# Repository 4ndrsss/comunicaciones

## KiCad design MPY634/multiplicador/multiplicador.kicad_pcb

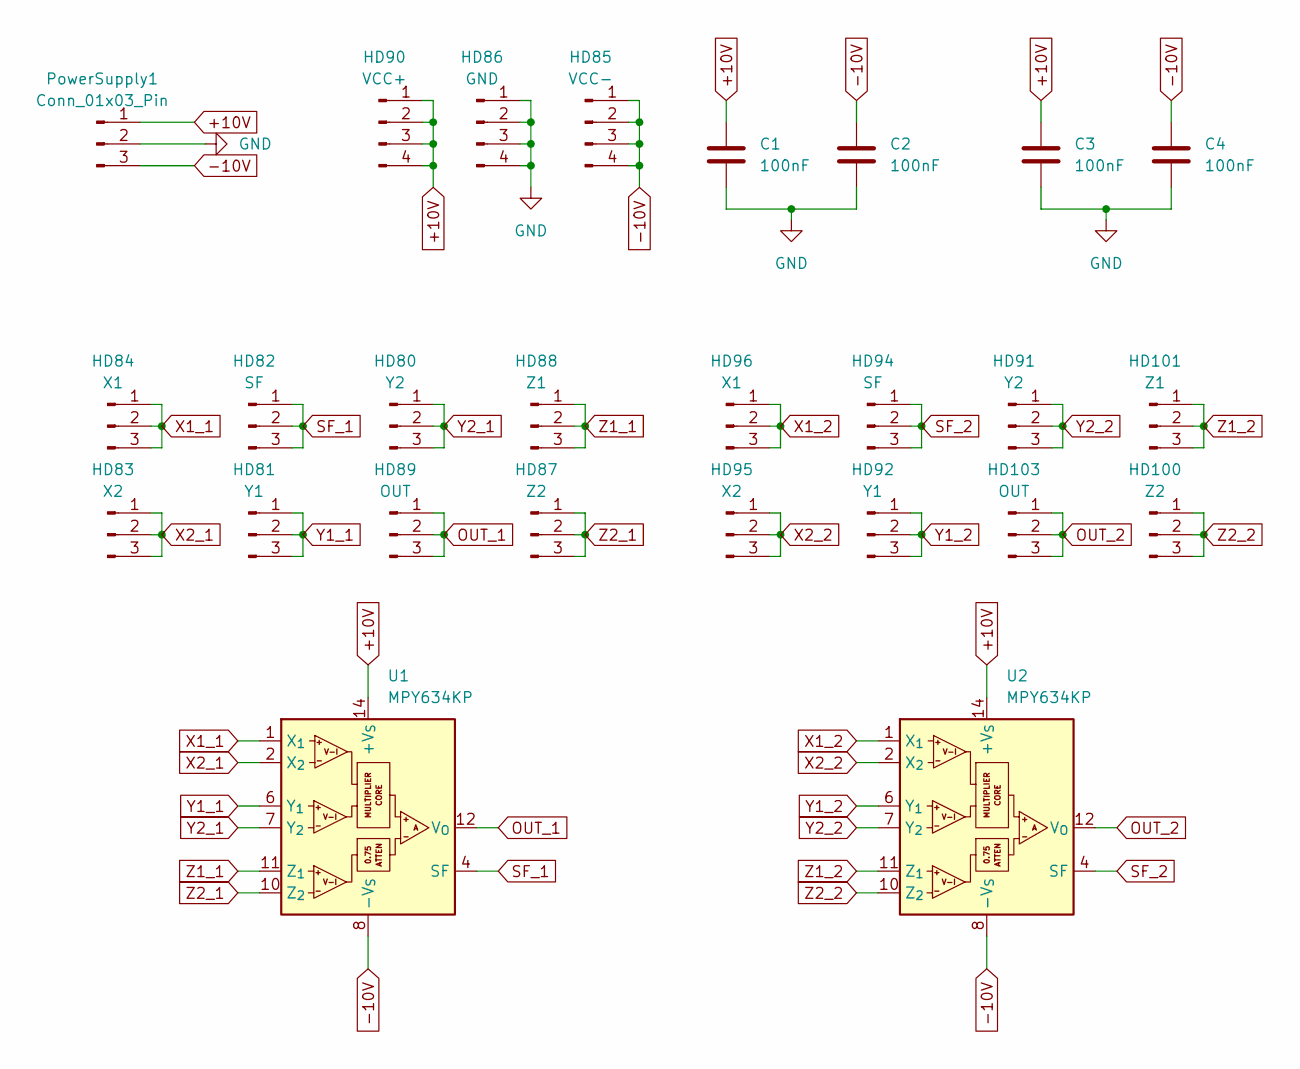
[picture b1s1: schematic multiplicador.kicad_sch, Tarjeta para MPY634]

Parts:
C1, C2, C3, C4: 100nF; C_1206_3216Metric
HD80, HD91: Y2; Header 1x03P1.27MM
HD81, HD92: Y1; Header 1x03P1.27MM
HD82, HD94: SF; Header 1x03P1.27MM
HD83, HD95: X2; Header 1x03P1.27MM
HD84, HD96: X1; Header 1x03P1.27MM
HD85: VCC-; Header 1x04P1.27MM
HD86: GND; Header 1x04P1.27MM
HD87, HD100: Z2; Header 1x03P1.27MM
HD88, HD101: Z1; Header 1x03P1.27MM
HD89, HD103: OUT; Header 1x03P1.27MM
HD90: VCC+; Header 1x04P1.27MM
PowerSupply1: Conn_01x03_Pin; KF301 _3_P5MM
U1, U2: MPY634KP; DIP-14_W7.62mm

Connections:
+10V: C1.1, C3.1, HD90.1, HD90.2, HD90.3, HD90.4, PowerSupply1.1, U1.14 (+V_{S}), U2.14 (+V_{S})
-10V: C2.1, C4.1, HD85.1, HD85.2, HD85.3, HD85.4, PowerSupply1.3, U1.8 (-V_{S}), U2.8 (-V_{S})
GND: C1.2, C2.2, C3.2, C4.2, HD86.1, HD86.2, HD86.3, HD86.4, PowerSupply1.2
OUT_1: HD89.1, HD89.2, HD89.3, U1.12 (V_{O})
OUT_2: HD103.1, HD103.2, HD103.3, U2.12 (V_{O})
SF_1: HD82.1, HD82.2, HD82.3, U1.4 (SF)
SF_2: HD94.1, HD94.2, HD94.3, U2.4 (SF)
X1_1: HD84.1, HD84.2, HD84.3, U1.1 (X_{1})
X1_2: HD96.1, HD96.2, HD96.3, U2.1 (X_{1})
X2_1: HD83.1, HD83.2, HD83.3, U1.2 (X_{2})
X2_2: HD95.1, HD95.2, HD95.3, U2.2 (X_{2})
Y1_1: HD81.1, HD81.2, HD81.3, U1.6 (Y_{1})
Y1_2: HD92.1, HD92.2, HD92.3, U2.6 (Y_{1})
Y2_1: HD80.1, HD80.2, HD80.3, U1.7 (Y_{2})
Y2_2: HD91.1, HD91.2, HD91.3, U2.7 (Y_{2})
Z1_1: HD88.1, HD88.2, HD88.3, U1.11 (Z_{1})
Z1_2: HD101.1, HD101.2, HD101.3, U2.11 (Z_{1})
Z2_1: HD87.1, HD87.2, HD87.3, U1.10 (Z_{2})
Z2_2: HD100.1, HD100.2, HD100.3, U2.10 (Z_{2})

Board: 2 copper layers, 26 parts (0 on the bottom side), 19 nets, no tracks yet.

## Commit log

2024-02-23 Add files via upload
    Version 1
